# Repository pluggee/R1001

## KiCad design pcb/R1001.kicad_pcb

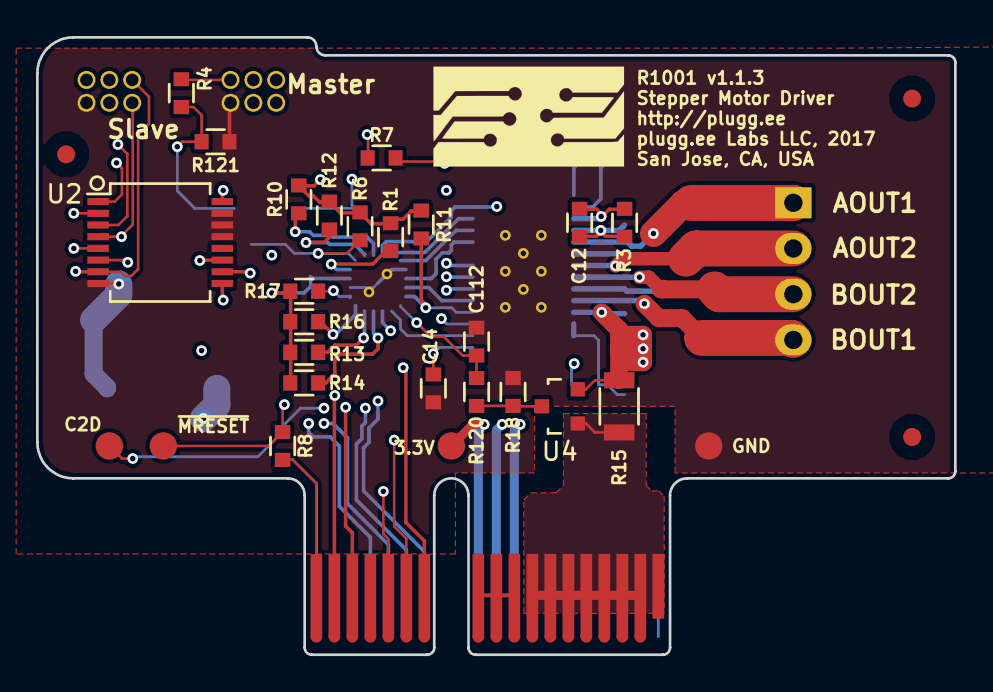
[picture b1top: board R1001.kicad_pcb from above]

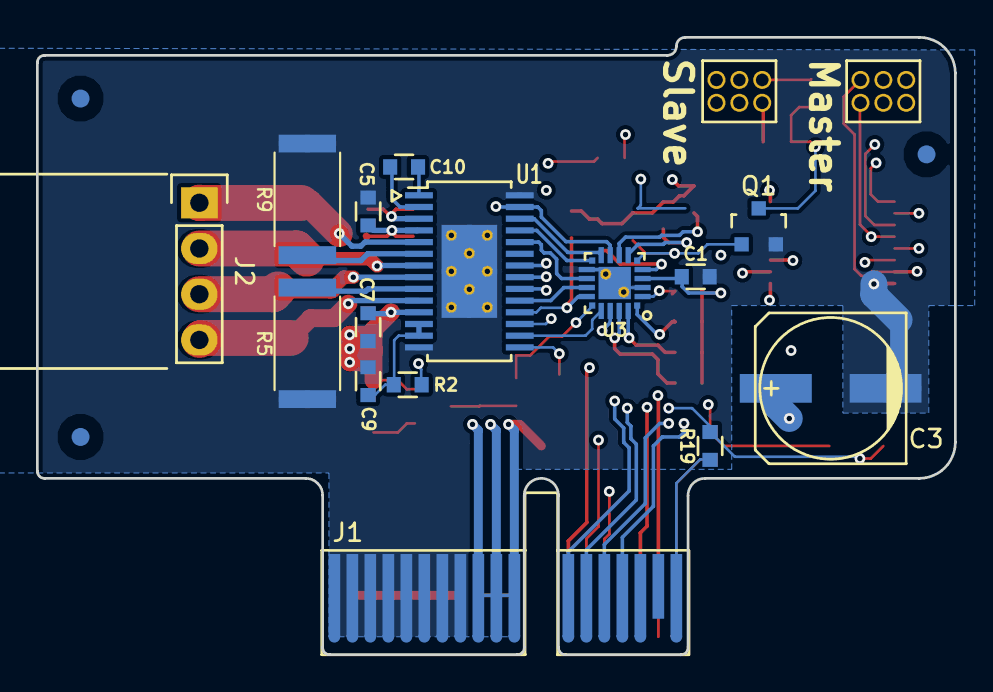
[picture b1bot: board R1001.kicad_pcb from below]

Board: 4 copper layers, 51.0 x 34.3 mm, 50 parts (20 on the bottom side), 47 nets.

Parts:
A1: ART; pluggeeLabsIcon-11x6
C1, C5, C7, C12: CC0603KRX7R9BB104; CAPC0603
C3: 47uF; c_elec_8x6.5
C9, C14, C112: CC0603KRX5R6BB105; CAPC0603
C10: CC0603KRX7R9BB103; CAPC0603
FID1, FID2, FID3, FID4, FID5, FID6: FIDTOP001
J1: PCIEXPRESS-X1
J2: CONN_01X04; 70553-0038
JMASTER1: SOCKMALE_02x03; SOCKET127P-02X03
JSLAVE1: SOCKMALE_02x03; SOCKET127P-02X03
Q1: Q_NMOS_GSD; SOT190P290X130X100-3
R1, R2, R6, R7, R10, R11, R12, R13, R14, R16, R17: RC0603FR-0710KL; RESC0603
R3: RC0603FR-071ML; RESC0603
R4, R18: RC0603FR-072K8L; RESC0603
R5, R9: RHC2512FTR250; RESC2512
R8, R19: RC0603FR-071KL; RESC0603
R15: ERJ-8CWFR050V; RESC1206
R120, R121: RC0603FR-07100KL; RESC0603
TP1, TP2, TP3, TP4: TestPoint; TestPoint000
U1: DRV8825; SOP65P970X440X120-28NT518X310
U2: 74LS157; SOP65P620X530X200-16
U3: EFM8BB10F8G; QFN50P300X300X75-20NT170X170
U4: ZXCT1107; SOT190P290X130X100-3

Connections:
+3V3: C1.1, J1.B9, J1.B10, J1.B11, JMASTER1.6, R1.1, R6.1, R7.1, R10.1, R11.1, R12.1, R13.1, R14.1, R16.1, R17.1, TP1.1, U1.17, U2.16, U3.4
+5V: J1.A9, J1.A10, J1.A11
/C2D_CON: J1.B18, R19.1
/D1_AOUT1: J2.1, U1.5
/D1_AOUT2: J2.2, U1.7
/D1_BOUT1: J2.4, U1.10
/D1_BOUT2: J2.3, U1.8
/D1_CP1: C10.2, U1.1
/D1_CP2: C10.1, U1.2
/D1_ISENA: R9.1, U1.6
/D1_ISENB: R5.1, U1.9
/D1_V3P3: C14.1, U1.15
/D1_VCP: C12.2, R3.2, U1.3
/DIR: JMASTER1.3, U1.20, U2.9
/D_VREF: C9.1, R2.1, U1.12, U1.13
/HT_CON: J1.A1, J1.A2, J1.A3, J1.A4, J1.A5, J1.A6, J1.A7, J1.A8, R15.1, U4.1
/IVDD_SENSE: C112.1, R120.2, U3.16
/MCU_DECAY: U1.19, U3.14
/MCU_MODE0: U1.24, U3.13
/MCU_MODE1: U1.25, U3.11
/MCU_MODE2: U1.26, U3.10
/MCU_PWMVREF: R2.2, U3.18
/SLAVE_ENABLE: Q1.3, R4.2, R121.1, U2.1
/SLAVE_ENABLE_CON: JSLAVE1.6, R4.1
/STEP: JMASTER1.1, U1.22, U2.4
/S_DIR: JSLAVE1.3, U2.10
/S_STEP: JSLAVE1.1, U2.3
/S_~ENBL: JSLAVE1.2, U2.6
/~D1_FAULT: R11.2, U1.18, U3.15
/~D1_HOME: R7.2, U1.27, U3.9
/~ENBL: JMASTER1.2, U1.21, U2.7
/~MCU_DRESET: U1.16, U3.17
/~MRESET_CON: J1.A18, R8.2
C2D: Q1.1, R6.2, R19.2, TP4.1, U3.6
GND: C1.2, C3.2, C5.2, C7.2, C9.2, C14.2, C112.2, J1.B1, J1.B2, J1.B3, J1.B4, J1.B5, J1.B6, J1.B7, J1.B8, JMASTER1.5, JSLAVE1.5, Q1.2, R5.2, R9.2, R18.2, R121.2, TP2.1, U1.14, U1.28, U1.29, U2.8, U2.13, U2.14, U2.15, U3.3, U3.12, U3.21
HT: C3.1, C5.1, C7.1, C12.1, R3.1, R15.2, U1.4, U1.11, U4.2
ID0: J1.B12, R14.2, U3.19
ID1: J1.B13, R13.2, U3.20
ID2: J1.B14, R12.2, U3.7
ID3: J1.B15, R10.2, U3.8
unnamed: R18.1, R120.1, U4.3
PX1_DIR: J1.A12, U2.11
PX2_~ENBL: J1.A13, U2.5
PX3_STEP: J1.A14, U2.2
SCL: J1.A16, R17.2, U3.2
SDA: J1.A17, R16.2, U3.1
~MRESET: R1.2, R8.1, TP3.1, U3.5

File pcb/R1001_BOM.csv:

Reference;Quantity;Value;Footprint;Datasheet;Manufacturer;MPN;SKU;C;Tol;Vmax;Type;Res;Pwr
A1 ;1;ART;pluggee:pluggeeLabsIcon-11x6;
C10 ;1;CC0603KRX7R9BB103;Main:CAPC0603;;Yageo;CC0603KRX7R9BB103;GENERIC;10.0 nF;±10%;50.0V;X7R;;
C3 ;1;47uF;Capacitors_SMD:c_elec_8x6.5;;Nichicon;UWX1V470MCL1GB;STUFF;47 µF;±20%;35V;Aluminum;;
C1 C12 C5 C7 ;4;CC0603KRX7R9BB104;Main:CAPC0603;;Yageo;CC0603KRX7R9BB104;GENERIC;100 nF;±10%;50.0V;X7R;;
C112 C14 C9 ;3;CC0603KRX5R6BB105;Main:CAPC0603;;Yageo;CC0603KRX5R6BB105;GENERIC;1.00 µF;±10%;10.0V;X5R;;
FID1 FID2 FID3 FID4 FID5 FID6 ;6;FIDTOP001;Main:FIDTOP001;
J1 ;1;PCIEXPRESS-X1;Main:PCIEXPRESS-X1;;Amphenol FCI;10018784-10200TLF;STUFF;;;;;;
J2 ;1;CONN_01X04;Main:70553-0038;;Molex;70553-0038;STUFF;;;;;;
JMASTER1 JSLAVE1 ;2;SOCKMALE_02x03;Main:SOCKET127P-02X03;;Sullins Connector Solutions;GRPB032MWCN-RC;GENERIC;;;;;;
Q1 ;1;Q_NMOS_GSD;Main:SOT190P290X130X100-3;;NXP USA Inc.;2N7002P,215;STUFF;;;;;;
R120 R121 ;2;RC0603FR-07100KL;Main:RESC0603;;Yageo;RC0603FR-07100KL;STUFF;;±1%;;;100 kΩ;100 mW
R15 ;1;ERJ-8CWFR050V;Main:RESC1206;;Panasonic Electronic Components;ERJ-8CWFR050V;GENERIC;;±1%;;;0.05 Ω;1W
R18 R4 ;2;RC0603FR-072K8L;Main:RESC0603;;Yageo;RC0603FR-072K8L;GENERIC;;±1%;;;2.80 kΩ;100 mW
R1 R10 R11 R12 R13 R14 R16 R17 R2 R6 R7 ;11;RC0603FR-0710KL;Main:RESC0603;;Yageo;RC0603FR-0710KL;GENERIC;;±1%;;;10.0 kΩ;100 mW
R3 ;1;RC0603FR-071ML;Main:RESC0603;;Yageo;RC0603FR-071ML;GENERIC;;±1%;;;1.00 MΩ;100 mW
R19 R8 ;2;RC0603FR-071KL;Main:RESC0603;;Yageo;RC0603FR-071KL;GENERIC;;±1%;;;1.00 kΩ;100 mW
R5 R9 ;2;RHC2512FTR250;Main:RESC2512;;Stackpole Electronics Inc.;RHC2512FTR250;GENERIC;;±1%;;;0.25 Ω;2W
TP1 TP2 TP3 TP4 ;4;TestPoint;Main:TestPoint000;
U1 ;1;DRV8825;Main:SOP65P970X440X120-28NT518X310;;Texas Instruments;DRV8825PWPR;STUFF;;;;;;
U2 ;1;74LS157;Main:SOP65P620X530X200-16;;NXP Semiconductors;74LVC157APW,118;STUFF;;;;;;
U3 ;1;EFM8BB10F8G;Main:QFN50P300X300X75-20NT170X170;;Silicon Labs;EFM8BB10F8G-A-QFN20R;STUFF;;;;;;
U4 ;1;ZXCT1107;Main:SOT190P290X130X100-3;;Diodes Incorporated;ZXCT1107SA-7;STUFF;;;;;;

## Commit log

2016-07-02 added doc & firmware directories
2016-07-02 moved design to repo
2016-07-02 updated design, placed driver
2016-07-03 completed layout
2016-07-03 created solder mask opening for large heat sink on bottom layer
2016-07-03 optimized layout for thermal
2016-07-23 v1.0.0-beta complete
2016-07-23 added silk screen to motor pins
2016-08-19 added BOM
2016-09-07 released 1.02 beta to adjust assign busy bee I2C pins to 0.0 and 0.1
2016-09-11 added 1st cut firmware
2016-10-23 fixed driver current function, added .gitignore
2016-10-26 cleaned up many things, verified all functions bring up
2016-10-26 fixed 2000mA limiting of IDRVH and IDRVL registers
2016-12-06 layout wip
2016-12-09 ready for v1.0.3 release
2016-12-09 added pref file in fw
2016-12-22 updated BOM file
2017-01-11 updated BOM
2017-02-14 added MCU mem map and initial bootloader code
2017-02-15 got bootloader I2C to function, not tested yet with an application image, wip
2017-02-15 alpha release of bootloader, need to test it with a bootloader aware firmware
2017-02-15 added firmware compiled data to .gitignore
2017-02-16 added linker/compiler command line options from AN767, still getting an error
2017-02-16 updated for silabs support case
2017-02-16 fixed the linker problems, added CLASSES(CODE (C:0x400-C:0x1DFF)) OVERLAY(* ! ?CO?INFOBLOCK) SEGMENTS(?CO?INFOBLOCK (C:0x1DF5)) to linker arguments
2017-02-21 updated BL, flash functions work, still startup function doesnt work and cant get device out of bootloader, stuck in flash reset
2017-02-21 updated bootloader, now application firmware works!
2017-03-28 added silk screen, fixed SOP footprint for pin 1 silkscreen, fixed 50mil connector drill size
2017-03-28 exported gerbers, added legend
2017-03-28 recreated gerbers, cleaned up BOM
2017-03-28 fixed silk screen version to v1.1
2017-03-28 added ms excel export
2017-03-29 added SMT assembly files
2017-03-29 added extra FID, changed silkscreen version to 1.1.1
2017-03-31 fixed BOM, marked RC parts GENERIC
2017-04-12 fixed silk screen signal names
2017-04-14 read for version 1.1.2, crowdsupply build
2017-04-16 fixed PCB outline for DFM, more space for bonding connectors
2017-05-15 alpha release, test before deploy
